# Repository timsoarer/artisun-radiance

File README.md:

# artisun-radiance
Code and KiCad 6.0.5 project for an artificial sunrise system powered by Arduino. Author: Timothy Mavreshko

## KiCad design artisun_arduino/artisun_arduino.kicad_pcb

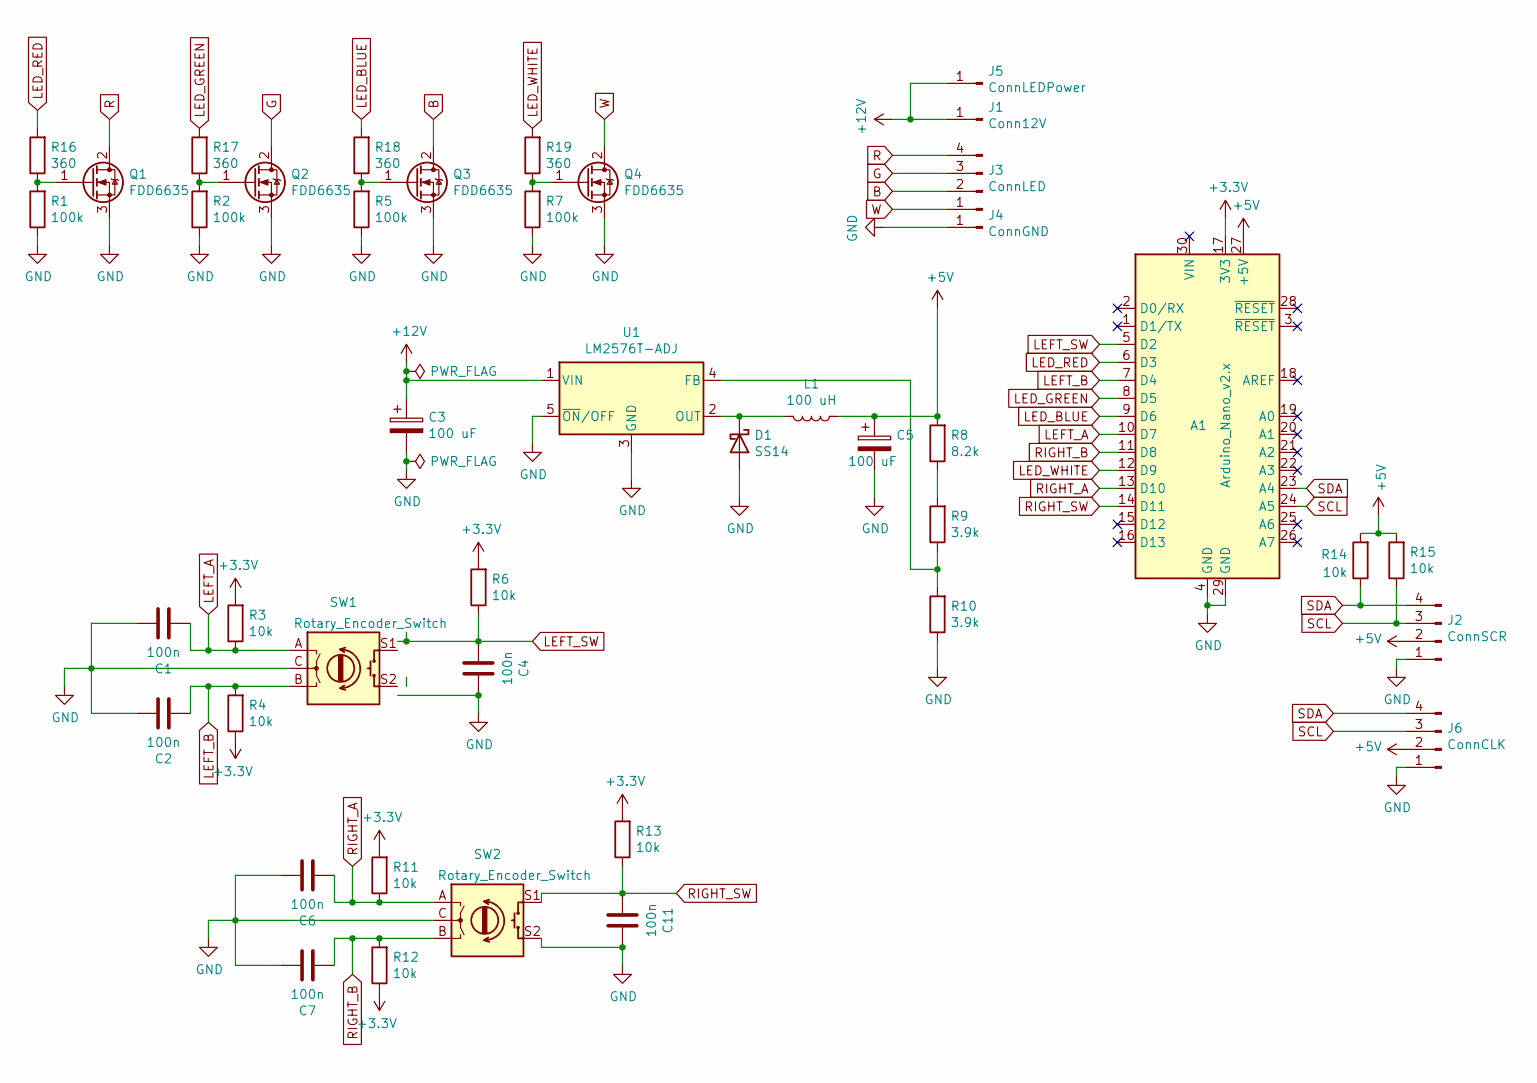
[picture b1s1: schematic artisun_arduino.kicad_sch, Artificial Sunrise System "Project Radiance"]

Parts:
A1: Arduino_Nano_v2.x; Arduino_Nano
C1, C2, C4, C6, C7, C11: 100n; C_0805_2012Metric
C3, C5: 100 uF; CP_Radial_D8.0mm_P3.80mm
D1: SS14; D_SMA_Handsoldering
J1: Conn12V; SolderWire-0.75sqmm_1x01_D1.25mm_OD2.3mm
J2: ConnSCR; SolderWire-0.75sqmm_1x04_P4.8mm_D1.25mm_OD2.3mm
J3: ConnLED; SolderWire-0.75sqmm_1x04_P4.8mm_D1.25mm_OD2.3mm
J4: ConnGND; SolderWire-0.75sqmm_1x01_D1.25mm_OD2.3mm
J5: ConnLEDPower; SolderWire-0.75sqmm_1x01_D1.25mm_OD2.3mm
J6: ConnCLK; SolderWire-0.75sqmm_1x04_P4.8mm_D1.25mm_OD2.3mm
L1: 100 uH; L_Radial_D10.0mm_P5.00mm_Fastron_07M
Q1, Q2, Q3, Q4: FDD6635; TO-252-2
R1, R2, R5, R7: 100k; R_0805_2012Metric
R3, R4, R6, R11, R12, R13, R14, R15: 10k; R_0805_2012Metric
R8: 8.2k; R_0805_2012Metric
R9, R10: 3.9k; R_0805_2012Metric
R16, R17, R18, R19: 360; R_0805_2012Metric
SW1, SW2: Rotary_Encoder_Switch; RotaryEncoder_Alps_EC12E-Switch_Vertical_H20mm
U1: LM2576T-ADJ; TO-220-5-SMD

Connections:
+3V3: A1.17 (3V3), R3.2, R4.1, R6.2, R11.2, R12.1, R13.2
+5V: A1.27 (+5V), C5.1, J2.2, J6.2, L1.1, R8.2, R14.2, R15.2
+12V: C3.1, J1.1, J5.1, U1.1 (VIN)
B: J3.2, Q3.2 (D)
G: J3.3, Q2.2 (D)
GND: A1.4 (GND), A1.29 (GND), C1.1, C2.1, C3.2, C4.1, C5.2, C6.1, C7.1, C11.1, D1.2 (A), J2.1, J4.1, J6.1, Q1.3 (S), Q2.3 (S), Q3.3 (S), Q4.3 (S), R1.1, R2.1, R5.1, R7.1, R10.1, SW1.C, SW1.S2, SW2.C, SW2.S2, U1.3 (GND), U1.5 (~ON/OFF)
LED_BLUE: A1.9 (D6), R18.2
LED_GREEN: A1.8 (D5), R17.2
LED_RED: A1.6 (D3), R16.2
LED_WHITE: A1.12 (D9), R19.2
LEFT_A: A1.10 (D7), C1.2, R3.1, SW1.A
LEFT_B: A1.7 (D4), C2.2, R4.2, SW1.B
LEFT_SW: A1.5 (D2), C4.2, R6.1, SW1.S1
unnamed: D1.1 (K), L1.2, U1.2 (OUT)
unnamed: Q1.1 (G), R1.2, R16.1
unnamed: Q2.1 (G), R2.2, R17.1
unnamed: Q3.1 (G), R5.2, R18.1
unnamed: Q4.1 (G), R7.2, R19.1
unnamed: R8.1, R9.2
unnamed: R9.1, R10.2, U1.4 (FB)
R: J3.4, Q1.2 (D)
RIGHT_A: A1.13 (D10), C6.2, R11.1, SW2.A
RIGHT_B: A1.11 (D8), C7.2, R12.2, SW2.B
RIGHT_SW: A1.14 (D11), C11.2, R13.1, SW2.S1
SCL: A1.24 (A5), J2.3, J6.3, R15.1
SDA: A1.23 (A4), J2.4, J6.4, R14.1
W: J3.1, Q4.2 (D)

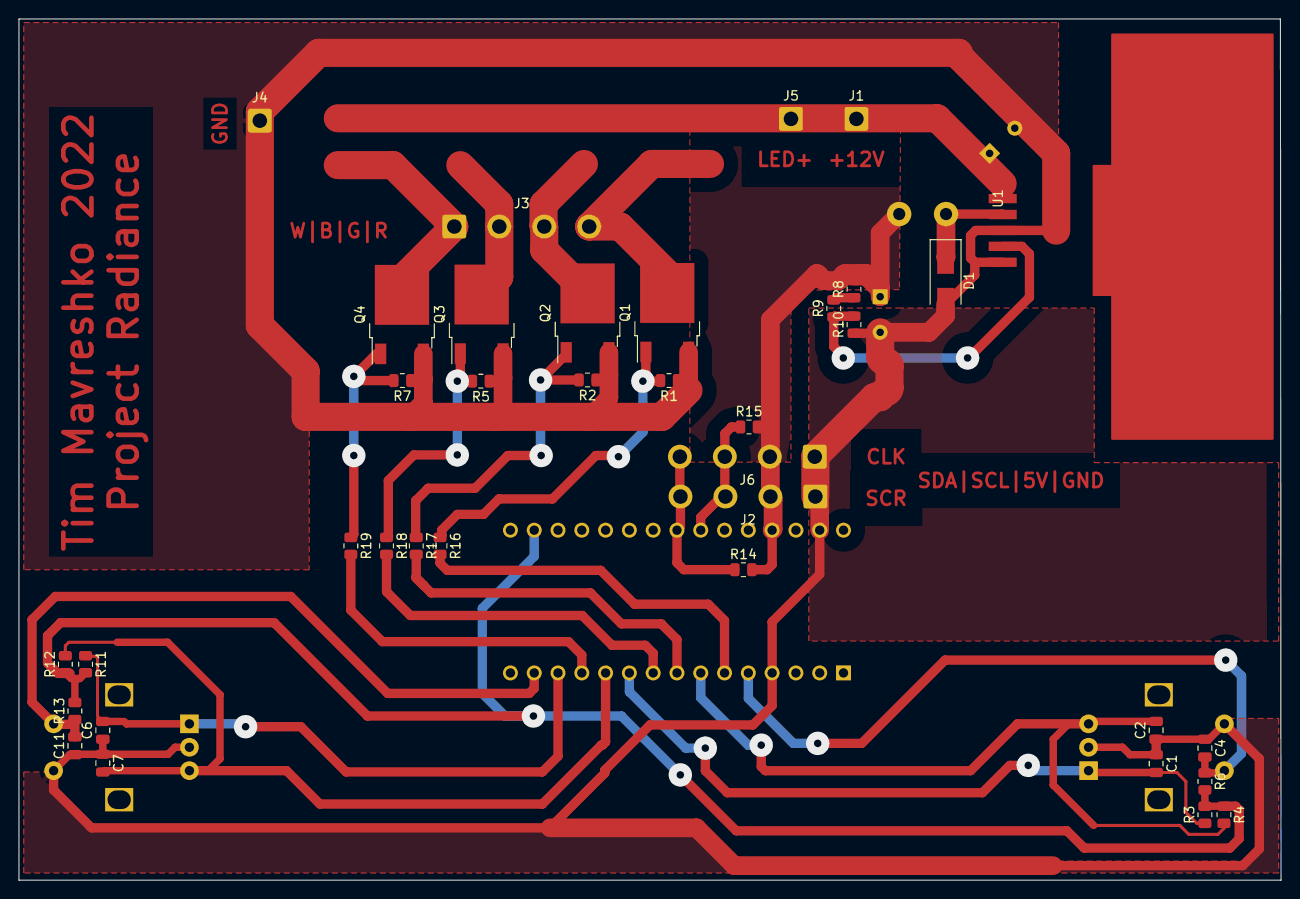
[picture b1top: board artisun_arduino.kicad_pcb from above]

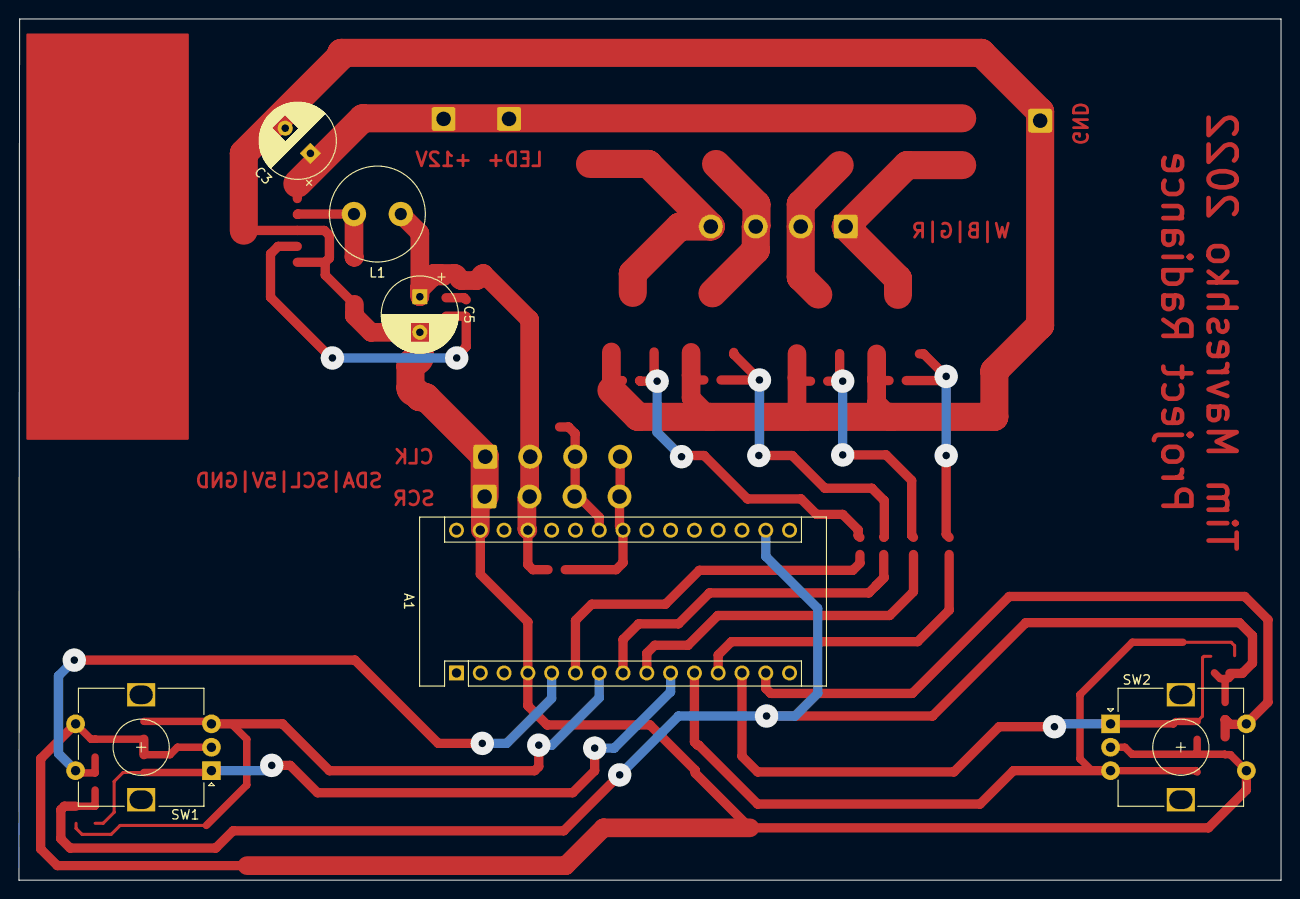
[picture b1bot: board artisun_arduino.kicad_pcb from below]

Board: 2 copper layers, 134.7 x 91.9 mm, 43 parts (6 on the bottom side), 27 nets.

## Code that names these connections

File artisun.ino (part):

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short brightness = 0; // The brightness of the LED strips. The value goes between 0 and WHITE_THRESHOLD + 100.

const byte
  LEFT_SW = 2,
  LEFT_A = 7,
  LEFT_B = 4,
  RIGHT_SW = 11, 
  RIGHT_A = 10,
  RIGHT_B = 8,
  LED_RED = 3,
  LED_GREEN = 5,
  LED_BLUE = 6,
  LED_WHITE = 9; // Arduino pins that are used for this project, constant names correspond to the pins' roles.

bool WakeupSoon() { // checks is the current time is exacly 30 minutes behind wakeup time or less.
  short currentTime = globalMinutes + globalHours * 60;
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  Wire.begin();

  //Initializes the required pins as input or output
  pinMode(LEFT_SW, INPUT);
  pinMode(LEFT_A, INPUT);
  pinMode(LEFT_B, INPUT);
  pinMode(RIGHT_SW, INPUT);
  pinMode(RIGHT_A, INPUT);
  pinMode(RIGHT_B, INPUT);
  
  pinMode(LED_RED, OUTPUT);
  pinMode(LED_GREEN, OUTPUT);
  pinMode(LED_BLUE, OUTPUT);
  pinMode(LED_WHITE, OUTPUT);
  
  //Sets an initial value for the previous cycle variables
  //Due to resistors pulling the input pin up to +3.3V by default, the values are essentially inverted
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
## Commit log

2022-06-20 Added the main code
2022-06-23 Added the KiCad schematics
    Made in KiCad 6.0.5. Contains schematics for Eeschema and one-sided PCB.
